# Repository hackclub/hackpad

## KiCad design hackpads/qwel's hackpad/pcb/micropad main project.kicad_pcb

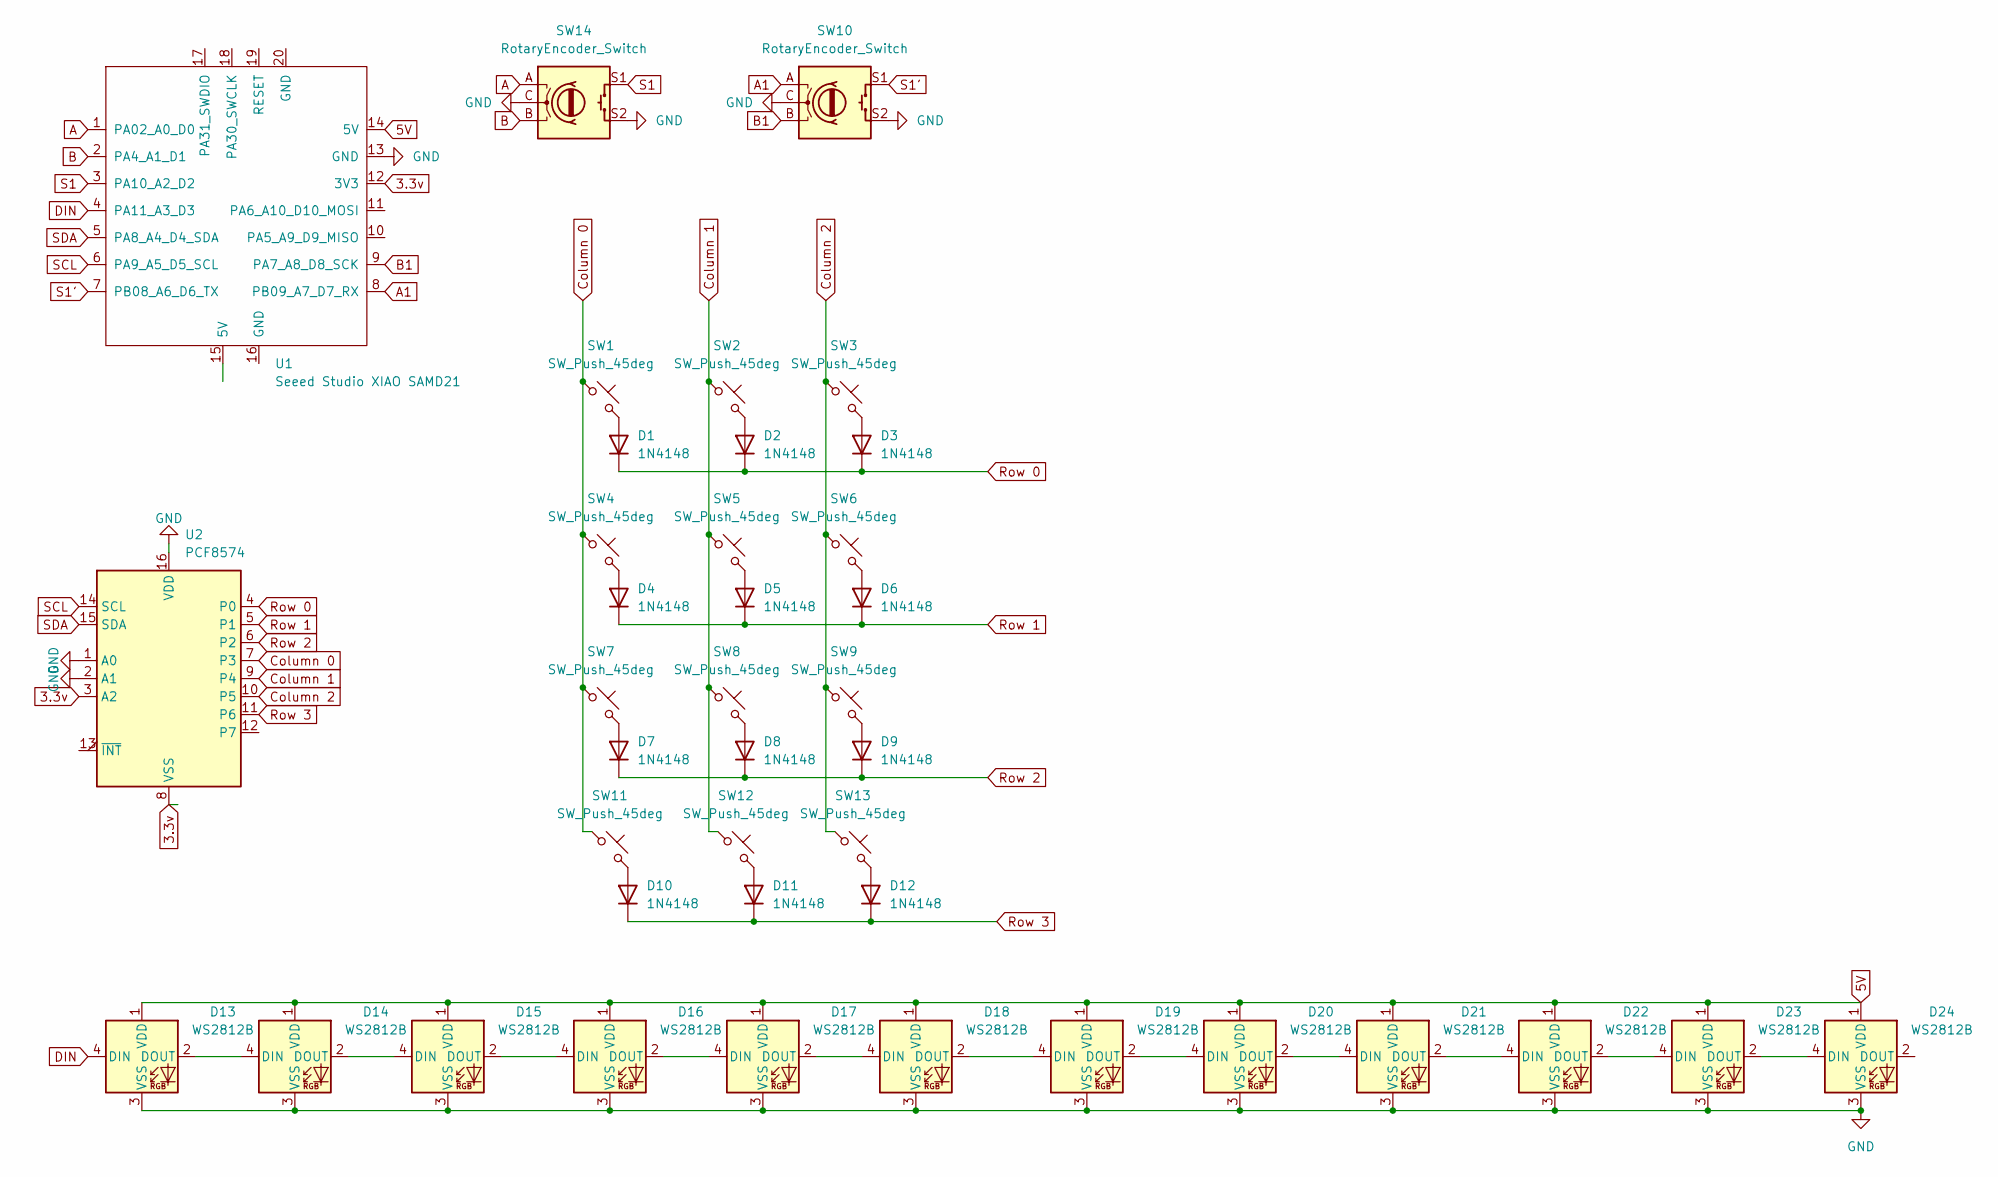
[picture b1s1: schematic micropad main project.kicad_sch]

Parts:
D1, D2, D3, D4, D5, D6, D7, D8, D9, D10, D11, D12: 1N4148; D_DO-35_SOD27_P7.62mm_Horizontal
D13, D14, D15, D16, D17, D18, D19, D20, D21, D22, D23, D24: WS2812B; LED_WS2812B_PLCC4_5.0x5.0mm_P3.2mm
SW1, SW2, SW3, SW4, SW5, SW6, SW7, SW8, SW9, SW11, SW12, SW13: SW_Push_45deg; SW_Cherry_MX_1.00u_PCB
SW10, SW14: RotaryEncoder_Switch; RotaryEncoder_Alps_EC11E-Switch_Vertical_H20mm
U1: Seeed Studio XIAO SAMD21; XIAO-Generic-Thruhole-14P-2.54-21X17.8MM
U2: PCF8574; CERDIP-16_W7.62mm_SideBrazed

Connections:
3.3v: U1.12 (3V3), U2.3 (A2), U2.8 (VSS)
5V: D13.1 (VDD), D14.1 (VDD), D15.1 (VDD), D16.1 (VDD), D17.1 (VDD), D18.1 (VDD), D19.1 (VDD), D20.1 (VDD), D21.1 (VDD), D22.1 (VDD), D23.1 (VDD), D24.1 (VDD), U1.14 (5V)
A: SW14.A, U1.1 (PA02_A0_D0)
A1: SW10.A, U1.8 (PB09_A7_D7_RX)
B: SW14.B, U1.2 (PA4_A1_D1)
B1: SW10.B, U1.9 (PA7_A8_D8_SCK)
Column 0: SW1.1, SW4.1, SW7.1, SW11.1, U2.7 (P3)
Column 1: SW2.1, SW5.1, SW8.1, SW12.1, U2.9 (P4)
Column 2: SW3.1, SW6.1, SW9.1, SW13.1, U2.10 (P5)
DIN: D13.4 (DIN), U1.4 (PA11_A3_D3)
GND: D13.3 (VSS), D14.3 (VSS), D15.3 (VSS), D16.3 (VSS), D17.3 (VSS), D18.3 (VSS), D19.3 (VSS), D20.3 (VSS), D21.3 (VSS), D22.3 (VSS), D23.3 (VSS), D24.3 (VSS), SW10.C, SW10.S2, SW14.C, SW14.S2, U1.13 (GND), U2.1 (A0), U2.2 (A1), U2.16 (VDD)
unnamed: D1.2 (A), SW1.2
unnamed: D2.2 (A), SW2.2
unnamed: D3.2 (A), SW3.2
unnamed: D4.2 (A), SW4.2
unnamed: D5.2 (A), SW5.2
unnamed: D6.2 (A), SW6.2
unnamed: D7.2 (A), SW7.2
unnamed: D8.2 (A), SW8.2
unnamed: D9.2 (A), SW9.2
unnamed: D10.2 (A), SW11.2
unnamed: D11.2 (A), SW12.2
unnamed: D12.2 (A), SW13.2
unnamed: D13.2 (DOUT), D14.4 (DIN)
unnamed: D14.2 (DOUT), D15.4 (DIN)
unnamed: D15.2 (DOUT), D16.4 (DIN)
unnamed: D16.2 (DOUT), D17.4 (DIN)
unnamed: D17.2 (DOUT), D18.4 (DIN)
unnamed: D18.2 (DOUT), D19.4 (DIN)
unnamed: D19.2 (DOUT), D20.4 (DIN)
unnamed: D20.2 (DOUT), D21.4 (DIN)
unnamed: D21.2 (DOUT), D22.4 (DIN)
unnamed: D22.2 (DOUT), D23.4 (DIN)
unnamed: D23.2 (DOUT), D24.4 (DIN)
Row 0: D1.1 (K), D2.1 (K), D3.1 (K), U2.4 (P0)
Row 1: D4.1 (K), D5.1 (K), D6.1 (K), U2.5 (P1)
Row 2: D7.1 (K), D8.1 (K), D9.1 (K), U2.6 (P2)
Row 3: D10.1 (K), D11.1 (K), D12.1 (K), U2.11 (P6)
S1: SW14.S1, U1.3 (PA10_A2_D2)
S1': SW10.S1, U1.7 (PB08_A6_D6_TX)
SCL: U1.6 (PA9_A5_D5_SCL), U2.14 (SCL)
SDA: U1.5 (PA8_A4_D4_SDA), U2.15 (SDA)

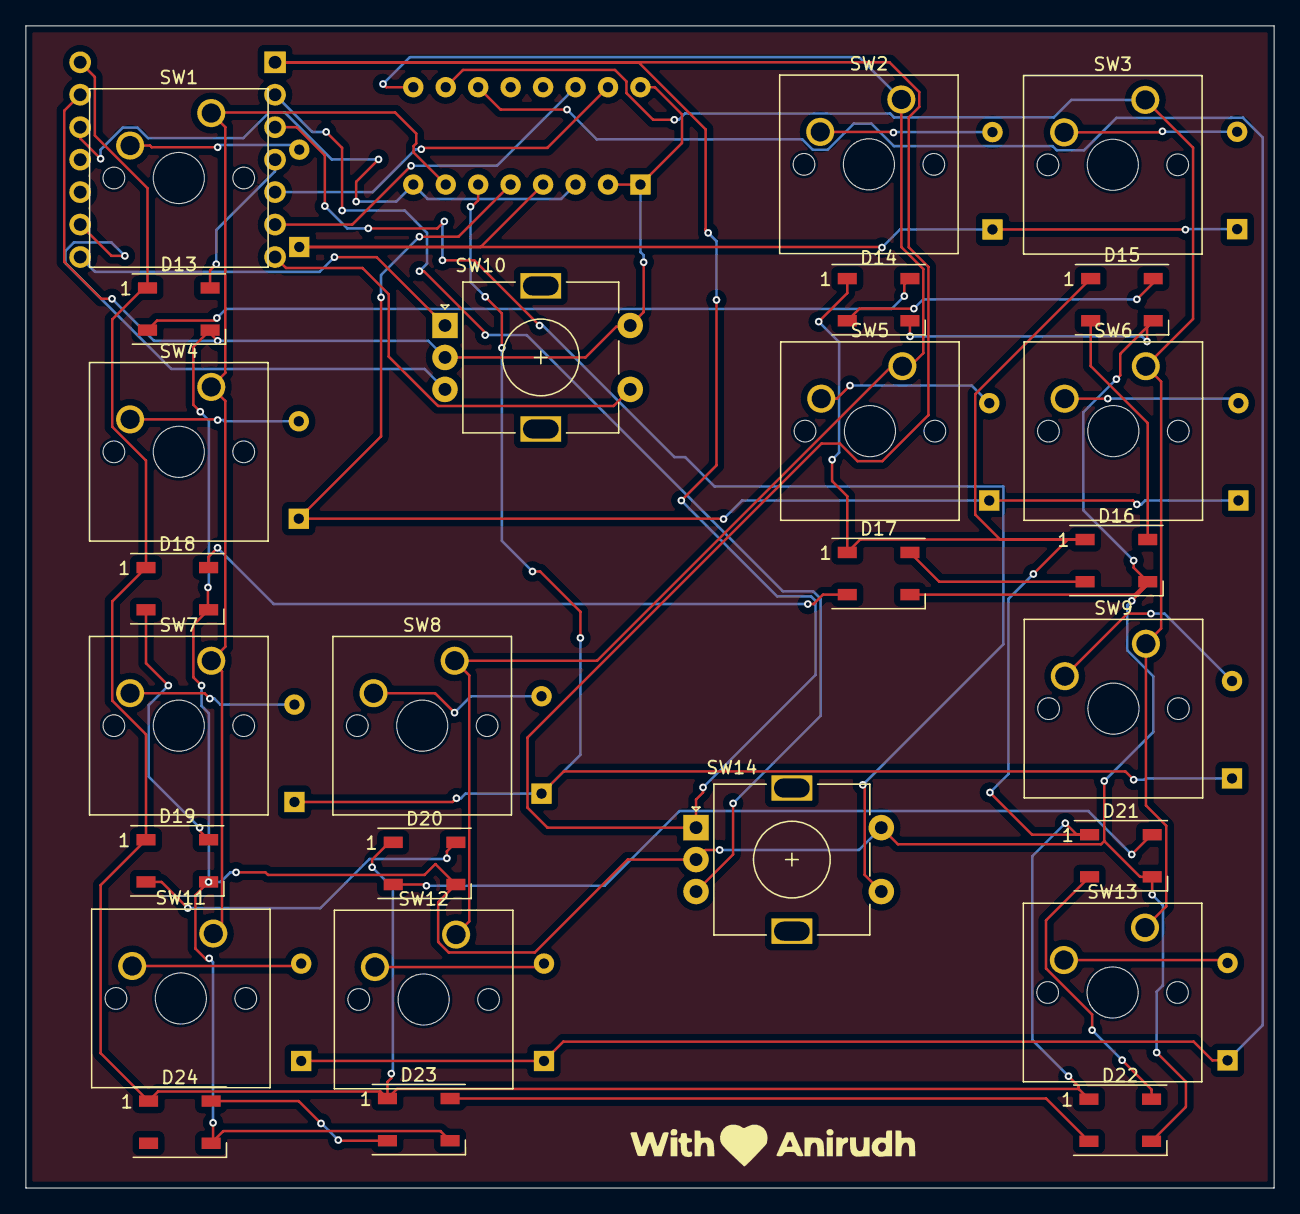
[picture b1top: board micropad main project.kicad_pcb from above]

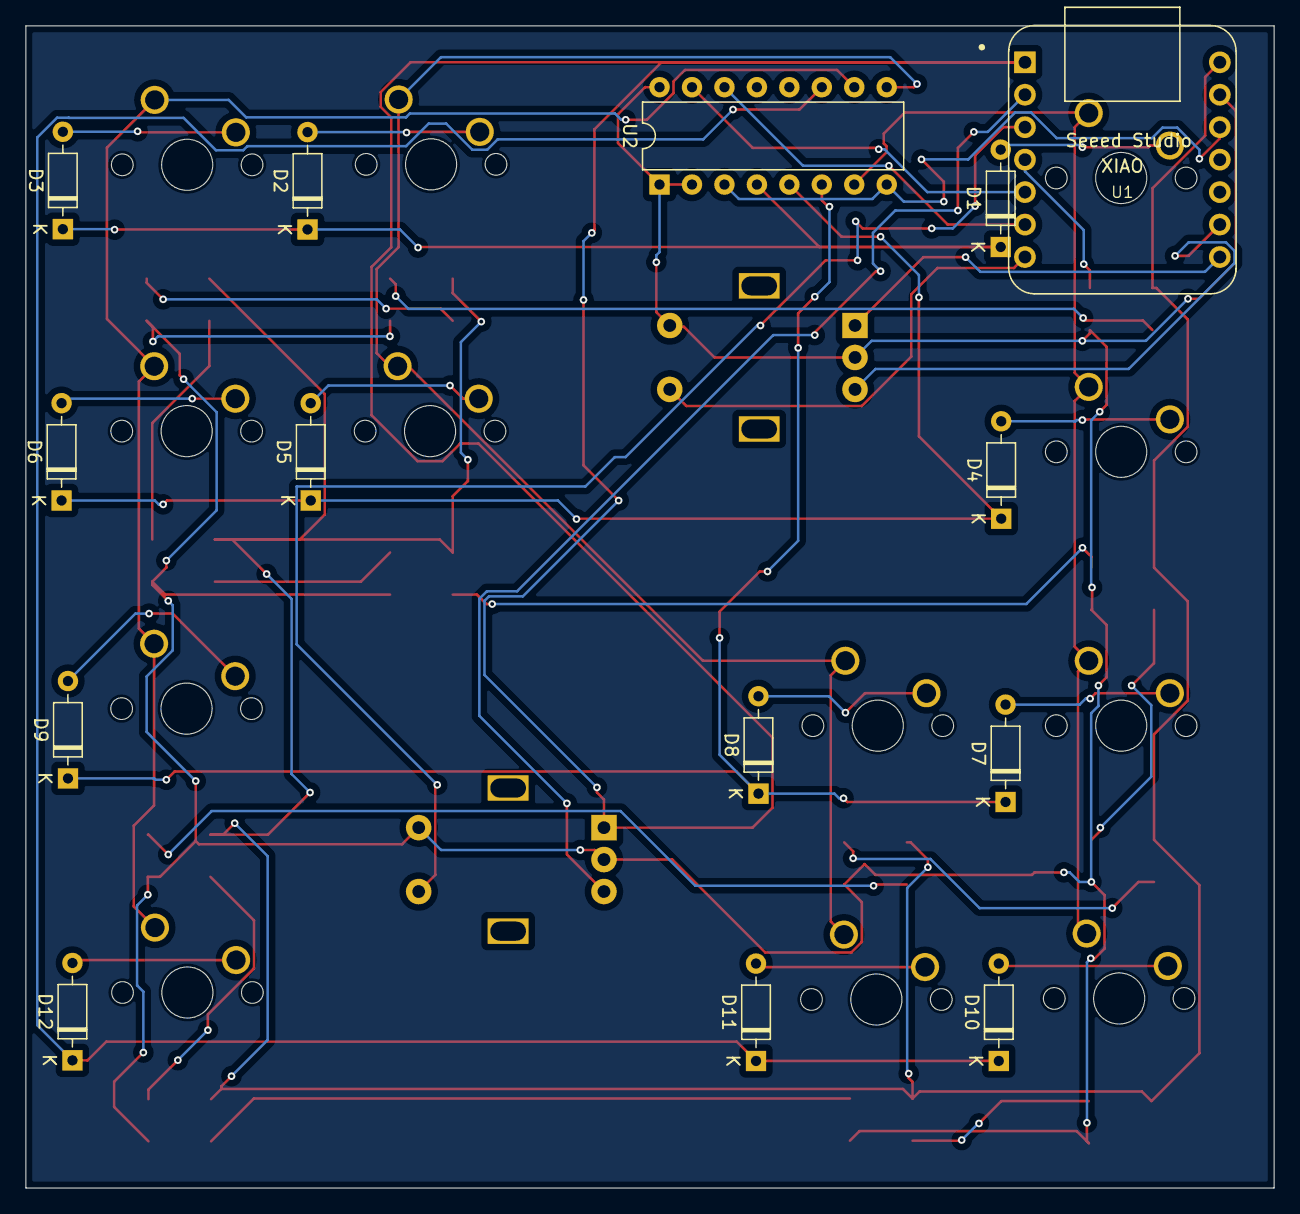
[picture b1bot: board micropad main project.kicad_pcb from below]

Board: 2 copper layers, 97.7 x 91.0 mm, 40 parts (14 on the bottom side), 42 nets.

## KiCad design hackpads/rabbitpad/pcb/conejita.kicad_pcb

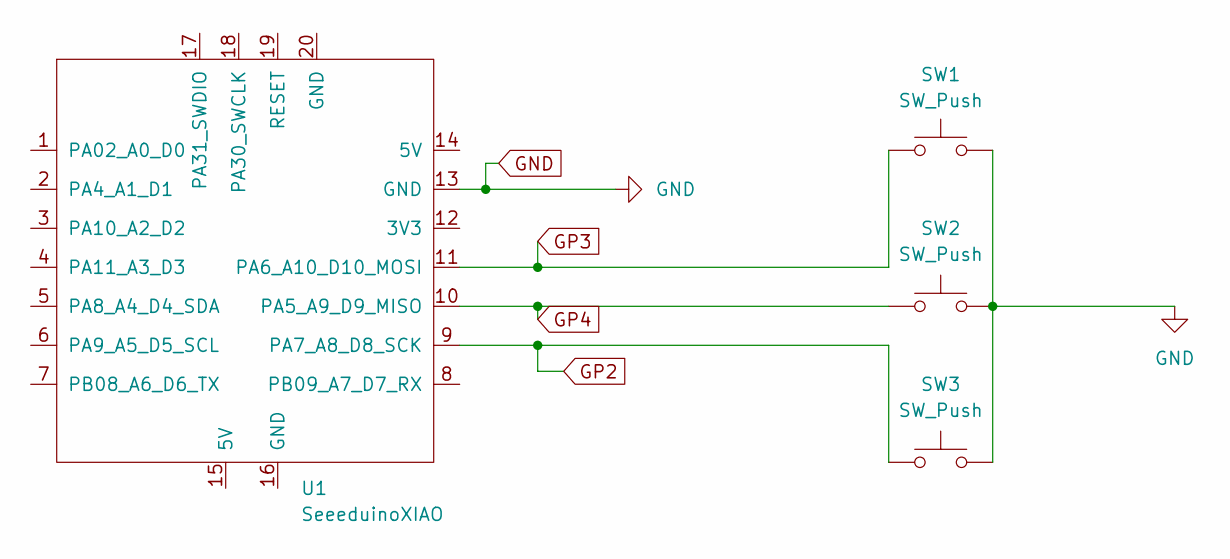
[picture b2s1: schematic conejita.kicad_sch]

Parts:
SW1, SW2, SW3: SW_Push; SW_Cherry_MX_1.00u_PCB
U1: SeeeduinoXIAO; XIAO-Generic-Thruhole-14P-2.54-21X17.8MM

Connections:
GND: SW1.2, SW2.2, SW3.2, U1.13 (GND)
unnamed: SW2.1, U1.10 (PA5_A9_D9_MISO)
unnamed: SW1.1, U1.11 (PA6_A10_D10_MOSI)
unnamed: SW3.1, U1.9 (PA7_A8_D8_SCK)

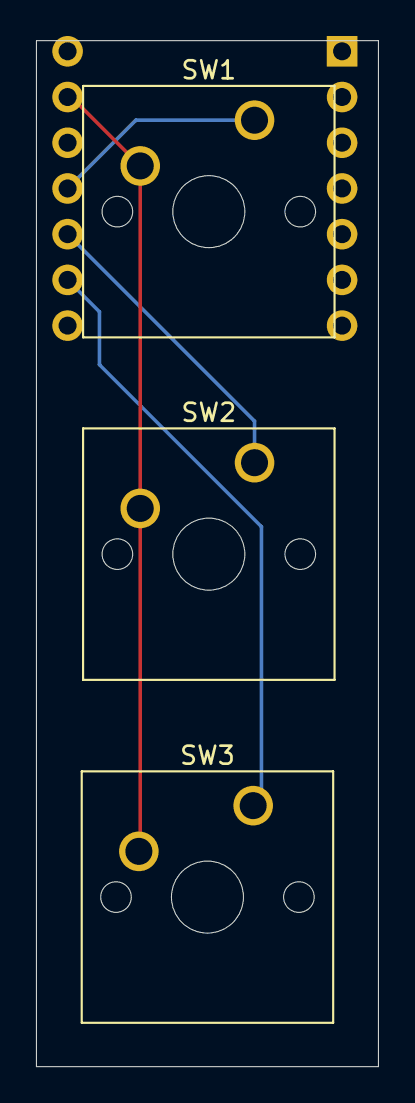
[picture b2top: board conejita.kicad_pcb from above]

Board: 2 copper layers, 19.0 x 57.0 mm, 4 parts (1 on the bottom side), 4 nets.

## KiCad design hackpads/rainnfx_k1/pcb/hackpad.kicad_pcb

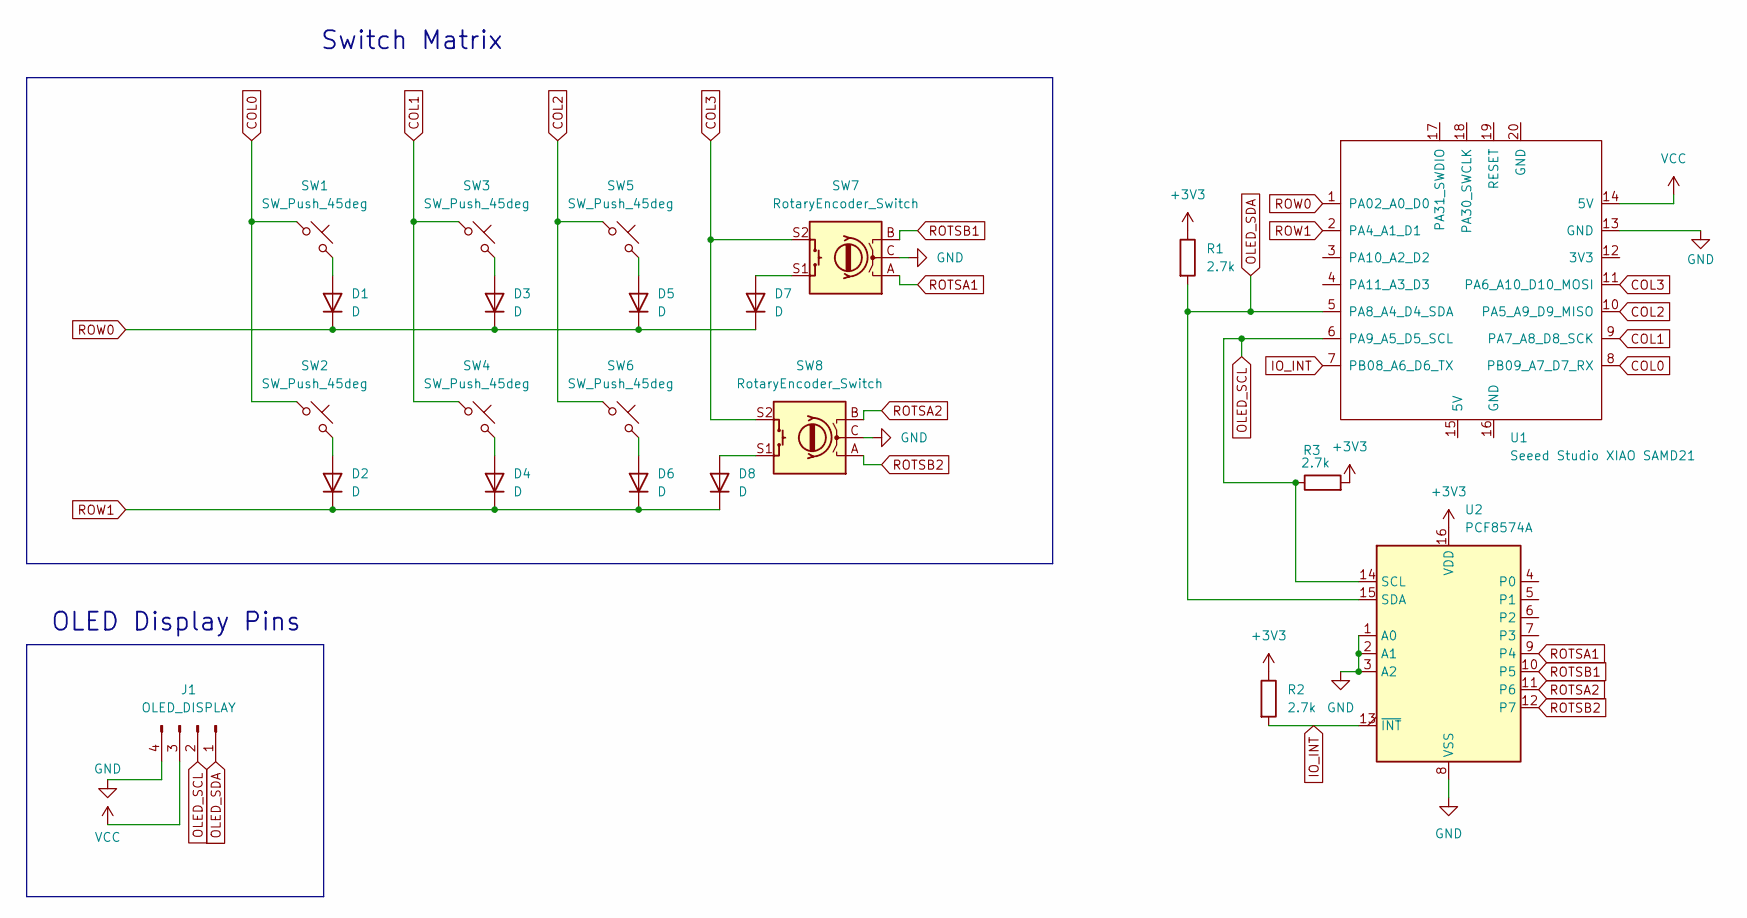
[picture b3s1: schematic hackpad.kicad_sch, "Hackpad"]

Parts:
D1, D2, D3, D4, D5, D6, D7, D8: D; D_DO-35_SOD27_P7.62mm_Horizontal
J1: OLED_DISPLAY; PinHeader_1x04_P2.54mm_Vertical
R1, R2, R3: 2.7k; R_Axial_DIN0207_L6.3mm_D2.5mm_P7.62mm_Horizontal
SW1, SW2, SW3, SW4, SW5, SW6: SW_Push_45deg; SW_Cherry_MX_1.00u_PCB
SW7, SW8: RotaryEncoder_Switch; RotaryEncoder_Alps_EC11E-Switch_Vertical_H20mm
U1: Seeed Studio XIAO SAMD21; XIAO-Generic-Thruhole-14P-2.54-21X17.8MM
U2: PCF8574A; N16_TEX

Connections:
+3V3: R1.1, R2.1, R3.2, U2.16 (VDD)
COL0: SW1.1, SW2.1, U1.8 (PB09_A7_D7_RX)
COL1: SW3.1, SW4.1, U1.9 (PA7_A8_D8_SCK)
COL2: SW5.1, SW6.1, U1.10 (PA5_A9_D9_MISO)
COL3: SW7.S2, SW8.S2, U1.11 (PA6_A10_D10_MOSI)
GND: J1.4, SW7.C, SW8.C, U1.13 (GND), U2.1 (A0), U2.2 (A1), U2.3 (A2), U2.8 (VSS)
IO_INT: R2.2, U1.7 (PB08_A6_D6_TX), U2.13 (~INT)
unnamed: D1.2 (A), SW1.2
unnamed: D2.2 (A), SW2.2
unnamed: D3.2 (A), SW3.2
unnamed: D4.2 (A), SW4.2
unnamed: D5.2 (A), SW5.2
unnamed: D6.2 (A), SW6.2
unnamed: D7.2 (A), SW7.S1
unnamed: D8.2 (A), SW8.S1
OLED_SCL: J1.2, R3.1, U1.6 (PA9_A5_D5_SCL), U2.14 (SCL)
OLED_SDA: J1.1, R1.2, U1.5 (PA8_A4_D4_SDA), U2.15 (SDA)
ROTSA1: SW7.A, U2.9 (P4)
ROTSA2: SW8.B, U2.11 (P6)
ROTSB1: SW7.B, U2.10 (P5)
ROTSB2: SW8.A, U2.12 (P7)
ROW0: D1.1 (K), D3.1 (K), D5.1 (K), D7.1 (K), U1.1 (PA02_A0_D0)
ROW1: D2.1 (K), D4.1 (K), D6.1 (K), D8.1 (K), U1.2 (PA4_A1_D1)
VCC: J1.3, U1.14 (5V)

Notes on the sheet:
Switch Matrix
OLED Display Pins

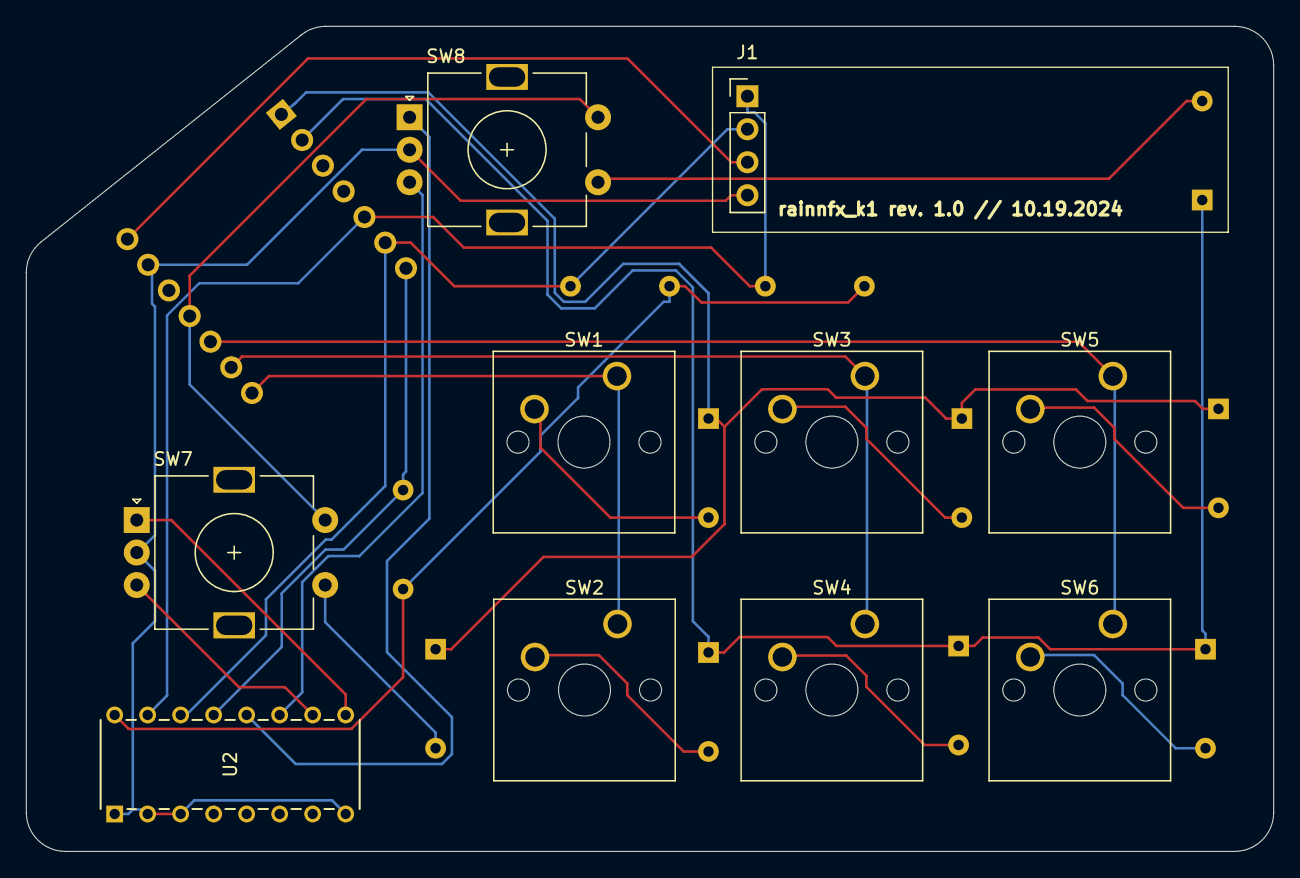
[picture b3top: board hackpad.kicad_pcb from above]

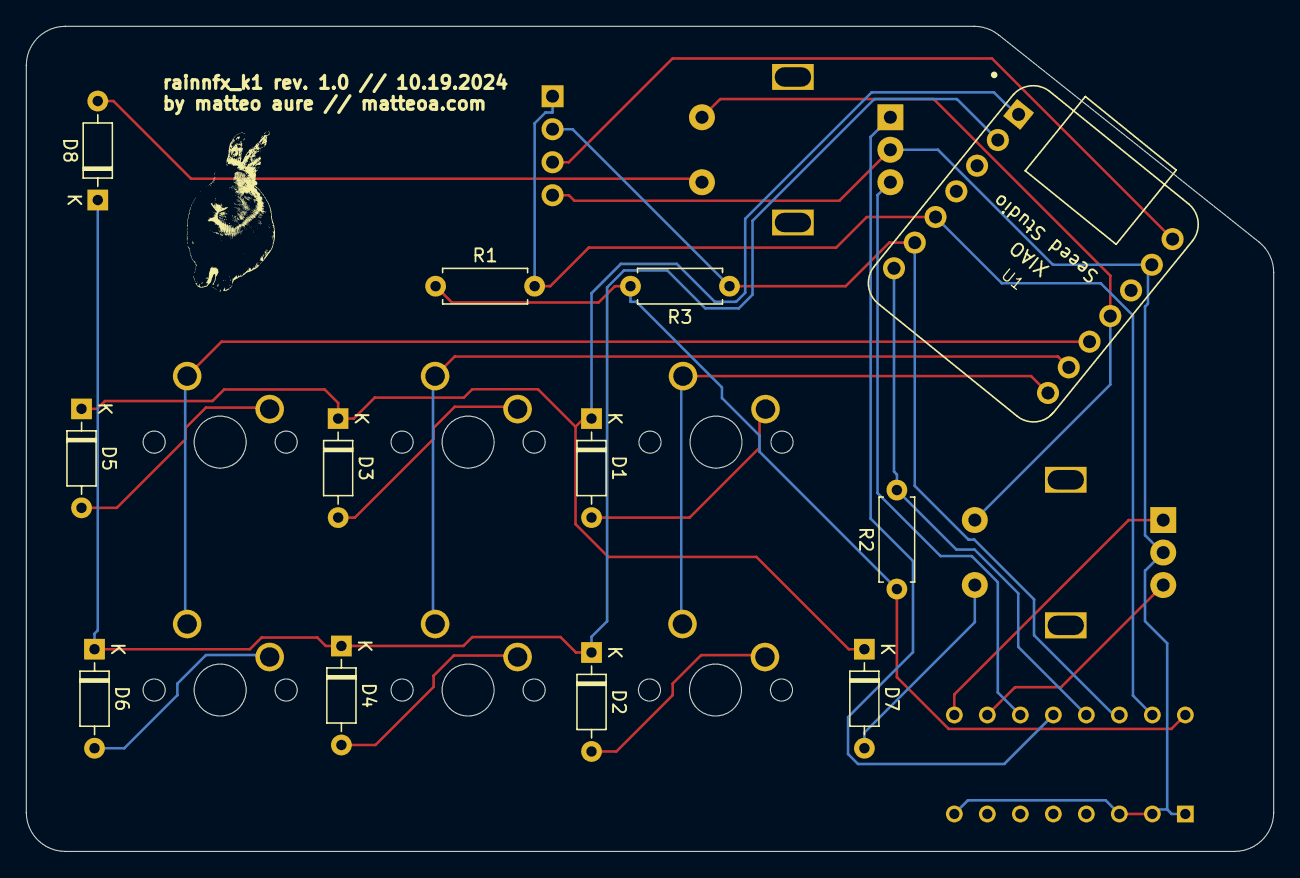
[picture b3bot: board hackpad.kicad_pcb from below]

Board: 2 copper layers, 96.0 x 63.5 mm, 22 parts (12 on the bottom side), 24 nets.

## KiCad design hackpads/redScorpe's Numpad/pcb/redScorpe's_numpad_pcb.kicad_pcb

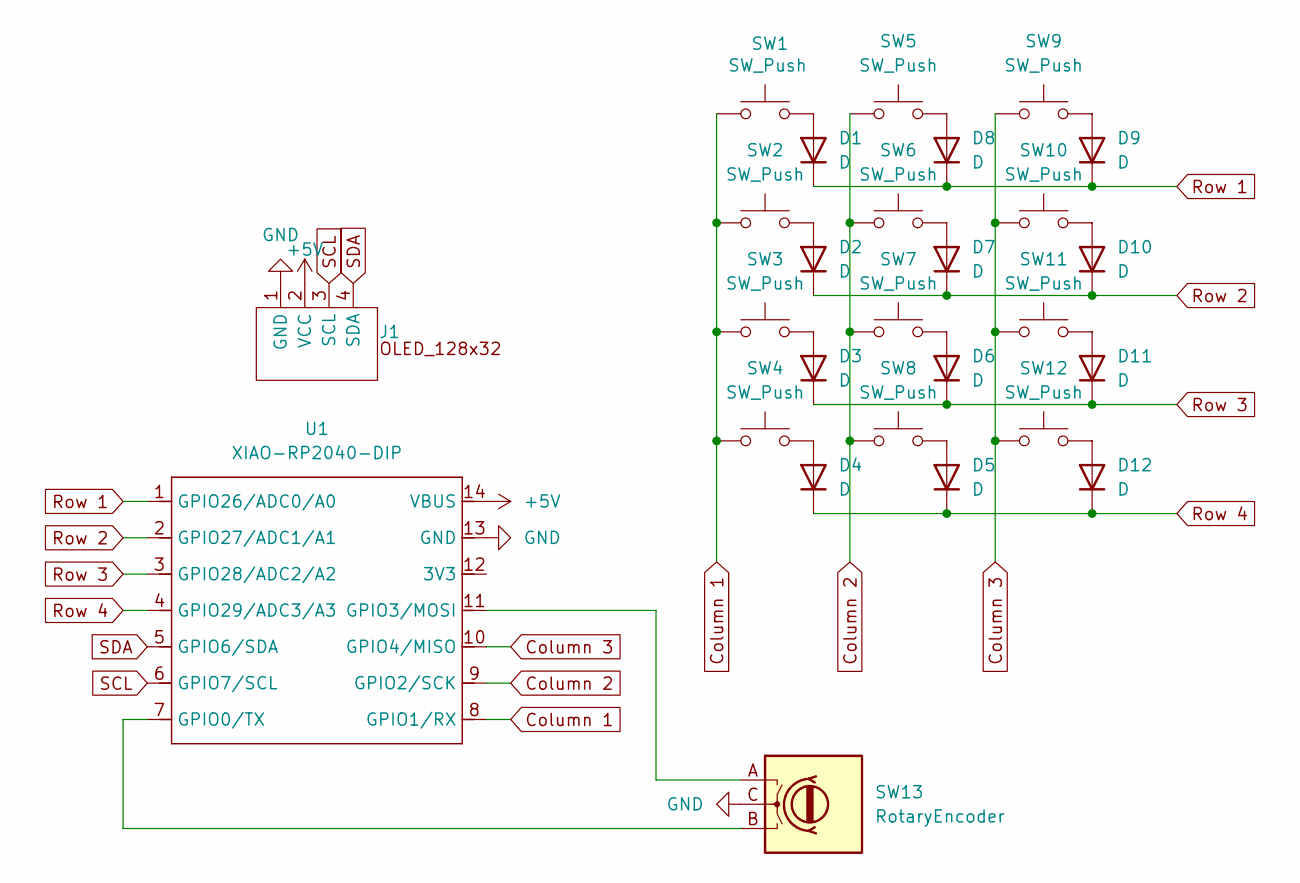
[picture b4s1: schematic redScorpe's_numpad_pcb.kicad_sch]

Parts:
D1, D2, D3, D4, D5, D6, D7, D8, D9, D10, D11, D12: D; D_DO-35_SOD27_P7.62mm_Horizontal
J1: SSD1306-0.91-OLED-4pin-128x32
SW1, SW2, SW3, SW4, SW5, SW6, SW7, SW8, SW9, SW10, SW11, SW12: SW_Push; SW_Cherry_MX_1.00u_PCB
SW13: RotaryEncoder; RotaryEncoder_Alps_EC11E_Vertical_H20mm_CircularMountingHol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
U1: XIAO-RP2040-DIP

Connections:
+5V: J1.2 (VCC), U1.14 (VBUS)
Column 1: SW1.1, SW2.1, SW3.1, SW4.1, U1.8 (GPIO1/RX)
Column 2: SW5.1, SW6.1, SW7.1, SW8.1, U1.9 (GPIO2/SCK)
Column 3: SW9.1, SW10.1, SW11.1, SW12.1, U1.10 (GPIO4/MISO)
GND: J1.1 (GND), SW13.C, U1.13 (GND)
unnamed: D1.2 (A), SW1.2
unnamed: D2.2 (A), SW2.2
unnamed: D3.2 (A), SW3.2
unnamed: D4.2 (A), SW4.2
unnamed: D5.2 (A), SW8.2
unnamed: D6.2 (A), SW7.2
unnamed: D7.2 (A), SW6.2
unnamed: D8.2 (A), SW5.2
unnamed: D9.2 (A), SW9.2
unnamed: D10.2 (A), SW10.2
unnamed: D11.2 (A), SW11.2
unnamed: D12.2 (A), SW12.2
unnamed: SW13.B, U1.7 (GPIO0/TX)
unnamed: SW13.A, U1.11 (GPIO3/MOSI)
Row 1: D1.1 (K), D8.1 (K), D9.1 (K), U1.1 (GPIO26/ADC0/A0)
Row 2: D2.1 (K), D7.1 (K), D10.1 (K), U1.2 (GPIO27/ADC1/A1)
Row 3: D3.1 (K), D6.1 (K), D11.1 (K), U1.3 (GPIO28/ADC2/A2)
Row 4: D4.1 (K), D5.1 (K), D12.1 (K), U1.4 (GPIO29/ADC3/A3)
SCL: J1.3 (SCL), U1.6 (GPIO7/SCL)
SDA: J1.4 (SDA), U1.5 (GPIO6/SDA)

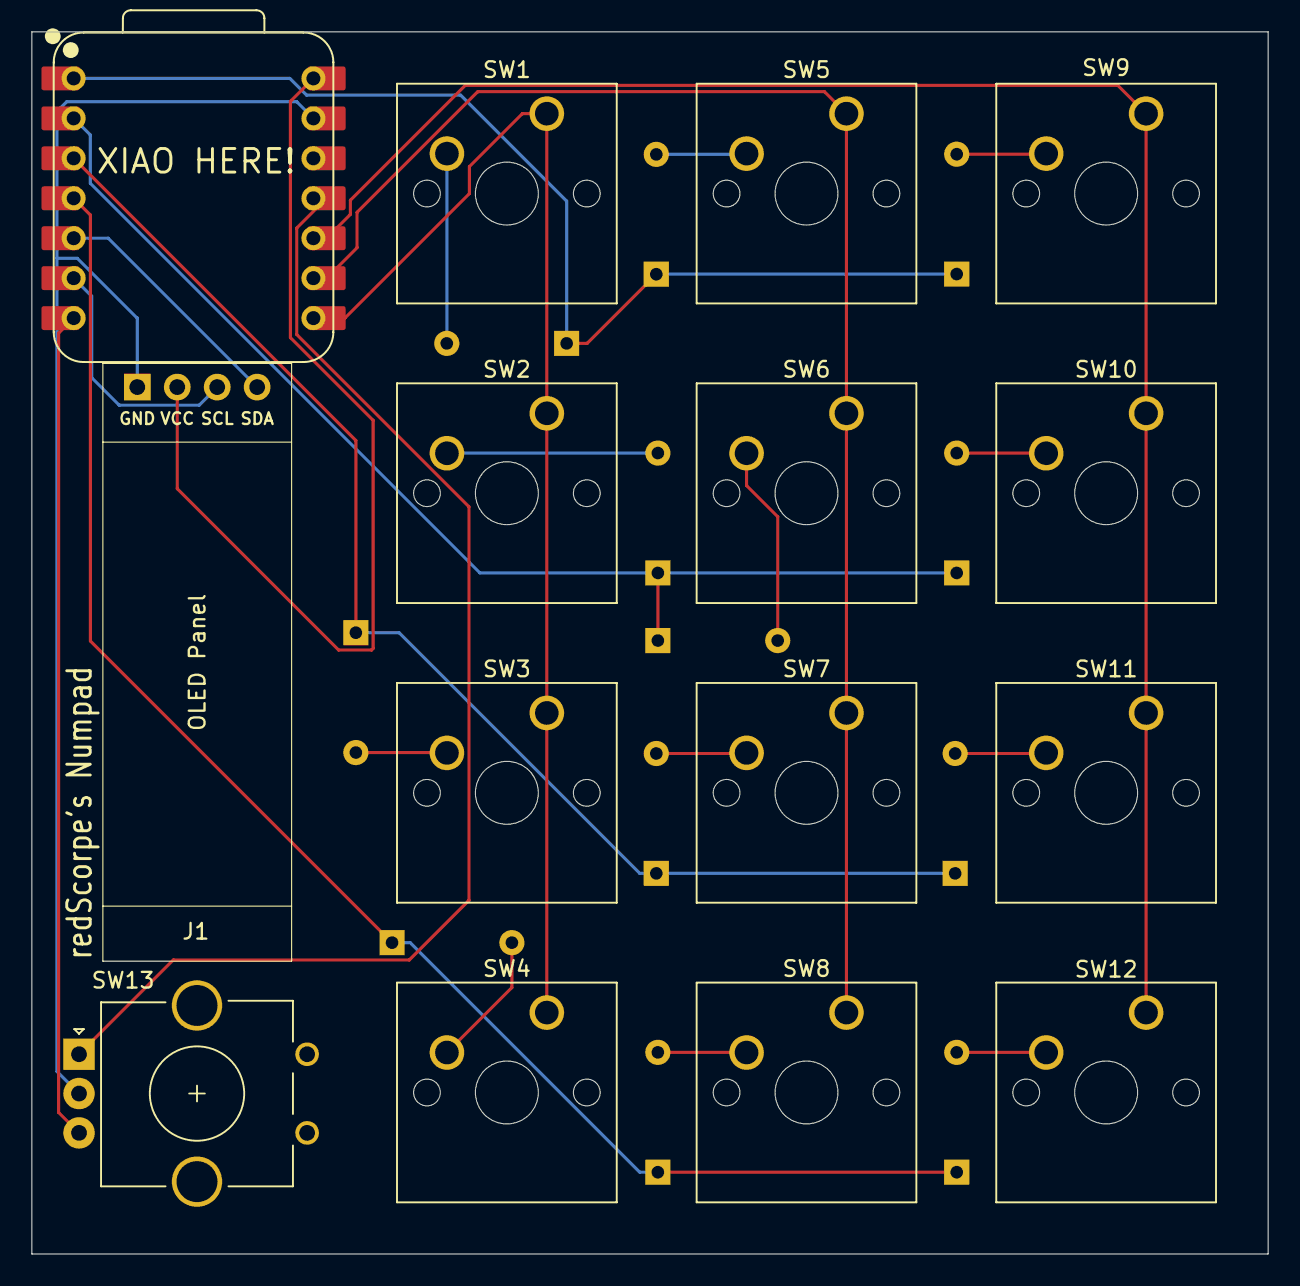
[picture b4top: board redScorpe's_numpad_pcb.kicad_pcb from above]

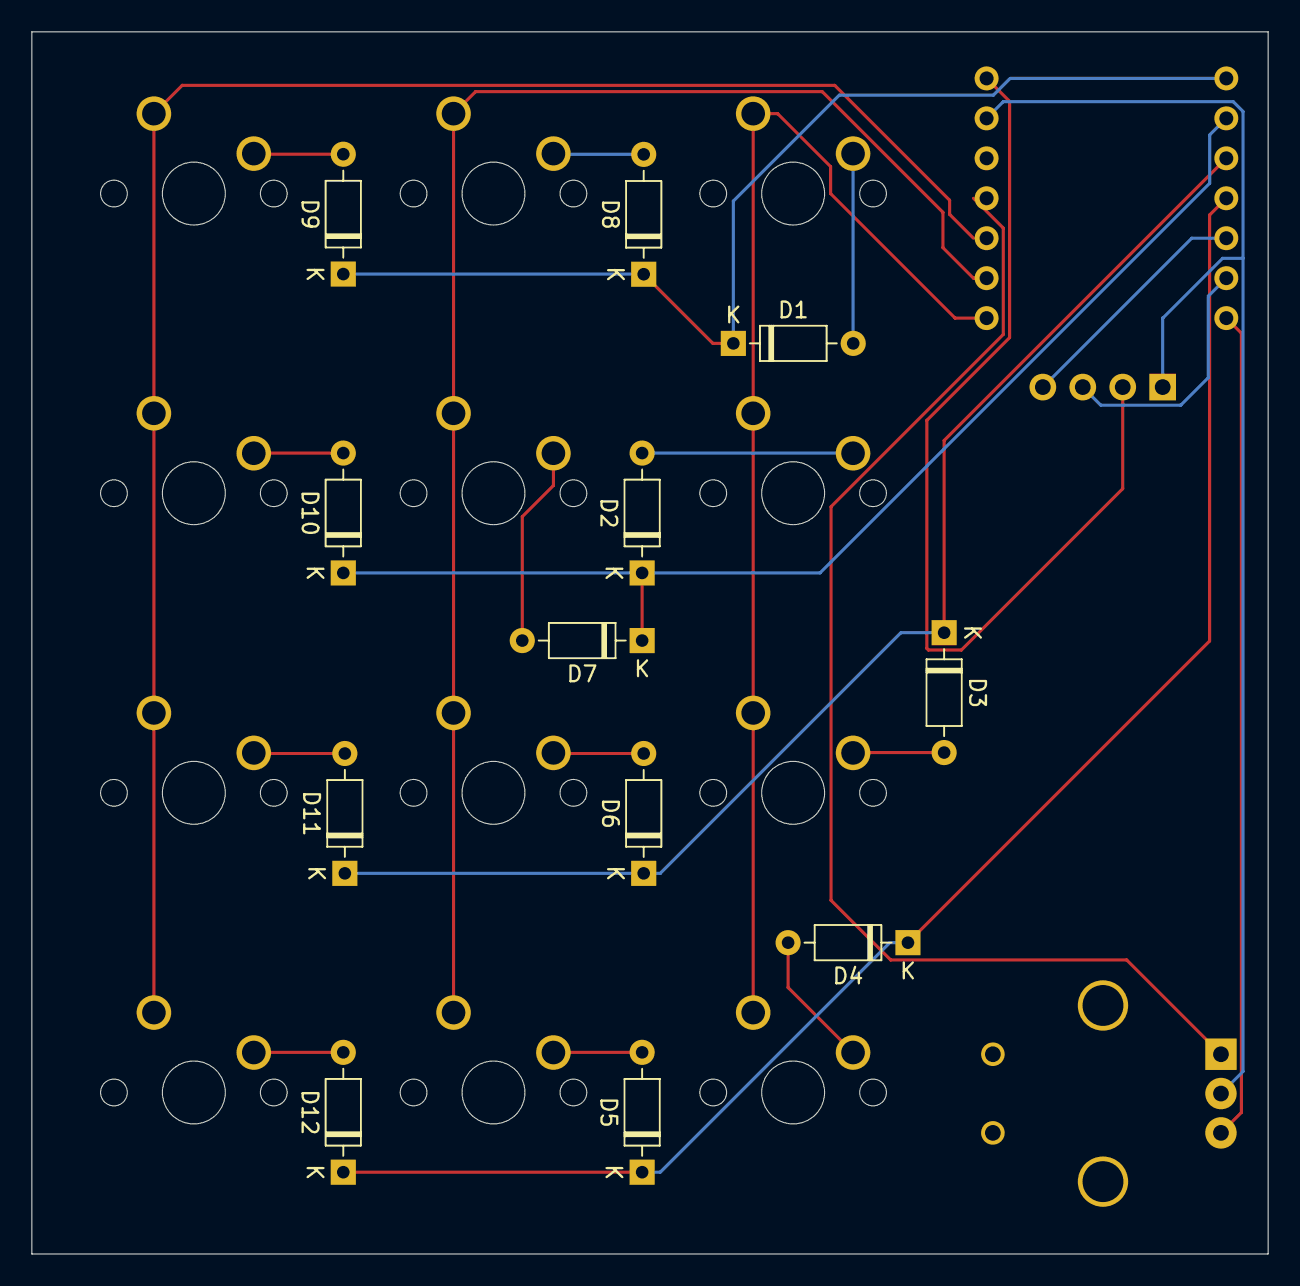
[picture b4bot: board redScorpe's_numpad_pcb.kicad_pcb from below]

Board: 2 copper layers, 78.6 x 77.7 mm, 27 parts (12 on the bottom side), 25 nets.

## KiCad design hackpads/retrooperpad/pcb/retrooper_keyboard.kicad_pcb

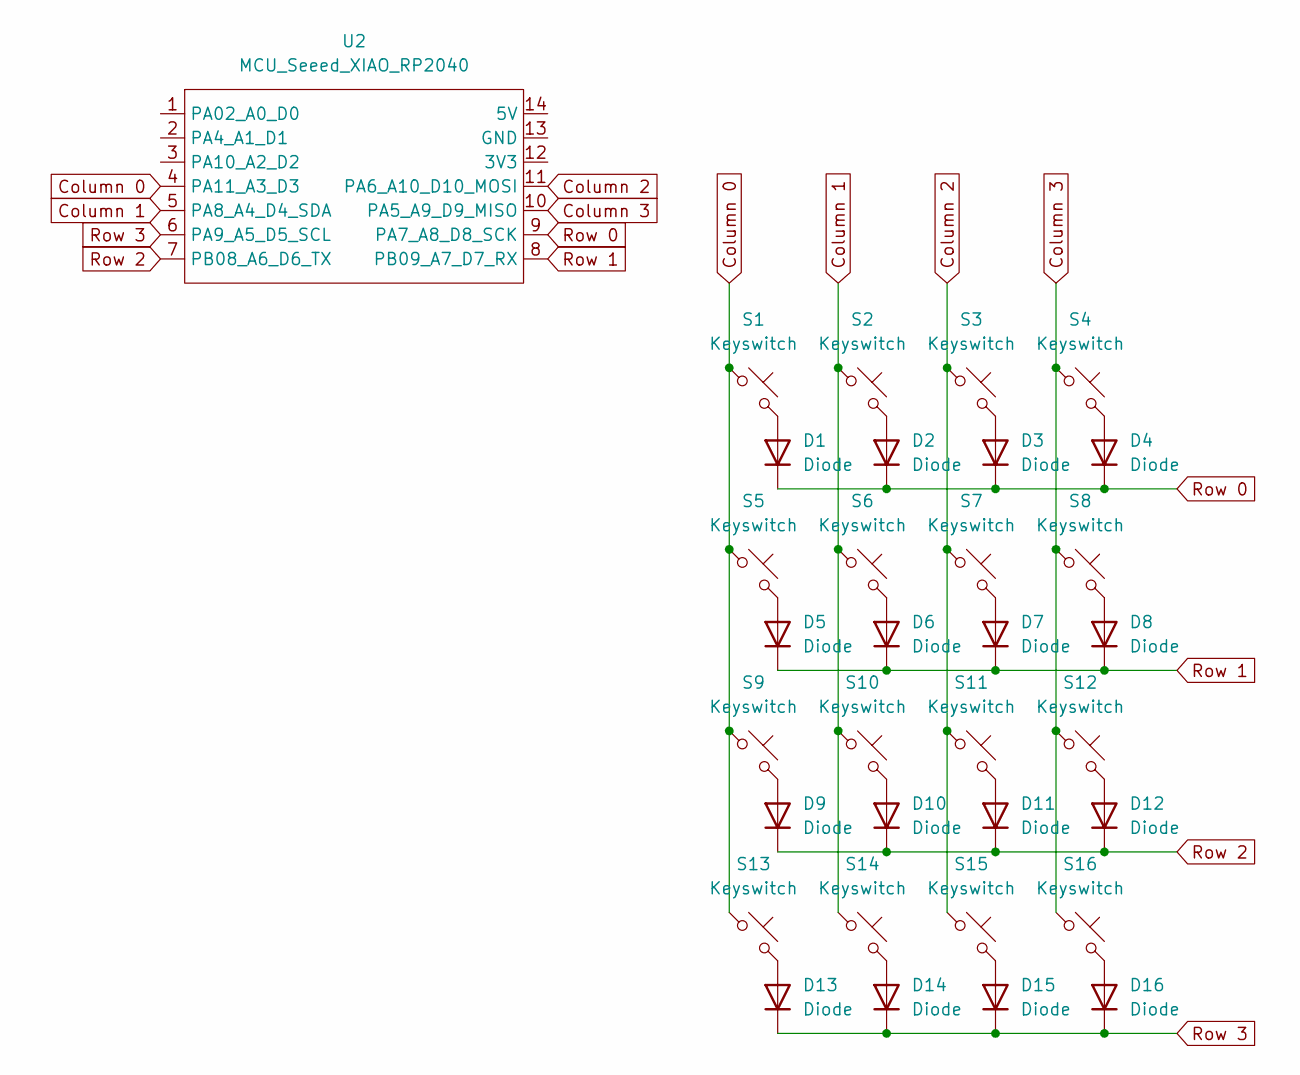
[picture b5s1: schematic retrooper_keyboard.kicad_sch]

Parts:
D1, D2, D3, D4, D5, D6, D7, D8, D9, D10, D11, D12, D13, D14, D15, D16: Diode; Diode_DO-35
S1, S2, S3, S4, S5, S6, S7, S8, S9, S10, S11, S12, S13, S14, S15, S16: Keyswitch; MX_PCB_1.00u
U2: MCU_Seeed_XIAO_RP2040; Seeed_XIAO_RP2040

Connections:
Column 0: S1.1, S5.1, S9.1, S13.1, U2.4 (PA11_A3_D3)
Column 1: S2.1, S6.1, S10.1, S14.1, U2.5 (PA8_A4_D4_SDA)
Column 2: S3.1, S7.1, S11.1, S15.1, U2.11 (PA6_A10_D10_MOSI)
Column 3: S4.1, S8.1, S12.1, S16.1, U2.10 (PA5_A9_D9_MISO)
unnamed: D1.2 (A), S1.2
unnamed: D2.2 (A), S2.2
unnamed: D3.2 (A), S3.2
unnamed: D4.2 (A), S4.2
unnamed: D5.2 (A), S5.2
unnamed: D6.2 (A), S6.2
unnamed: D7.2 (A), S7.2
unnamed: D8.2 (A), S8.2
unnamed: D9.2 (A), S9.2
unnamed: D10.2 (A), S10.2
unnamed: D11.2 (A), S11.2
unnamed: D12.2 (A), S12.2
unnamed: D13.2 (A), S13.2
unnamed: D14.2 (A), S14.2
unnamed: D15.2 (A), S15.2
unnamed: D16.2 (A), S16.2
Row 0: D1.1 (K), D2.1 (K), D3.1 (K), D4.1 (K), U2.9 (PA7_A8_D8_SCK)
Row 1: D5.1 (K), D6.1 (K), D7.1 (K), D8.1 (K), U2.8 (PB09_A7_D7_RX)
Row 2: D9.1 (K), D10.1 (K), D11.1 (K), D12.1 (K), U2.7 (PB08_A6_D6_TX)
Row 3: D13.1 (K), D14.1 (K), D15.1 (K), D16.1 (K), U2.6 (PA9_A5_D5_SCL)
